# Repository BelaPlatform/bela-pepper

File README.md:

# PEPPER

Pepper is a DIY solution for integrating Bela with modular and Eurorack synths. [Click here](https://github.com/BelaPlatform/bela-pepper/wiki) for more information.

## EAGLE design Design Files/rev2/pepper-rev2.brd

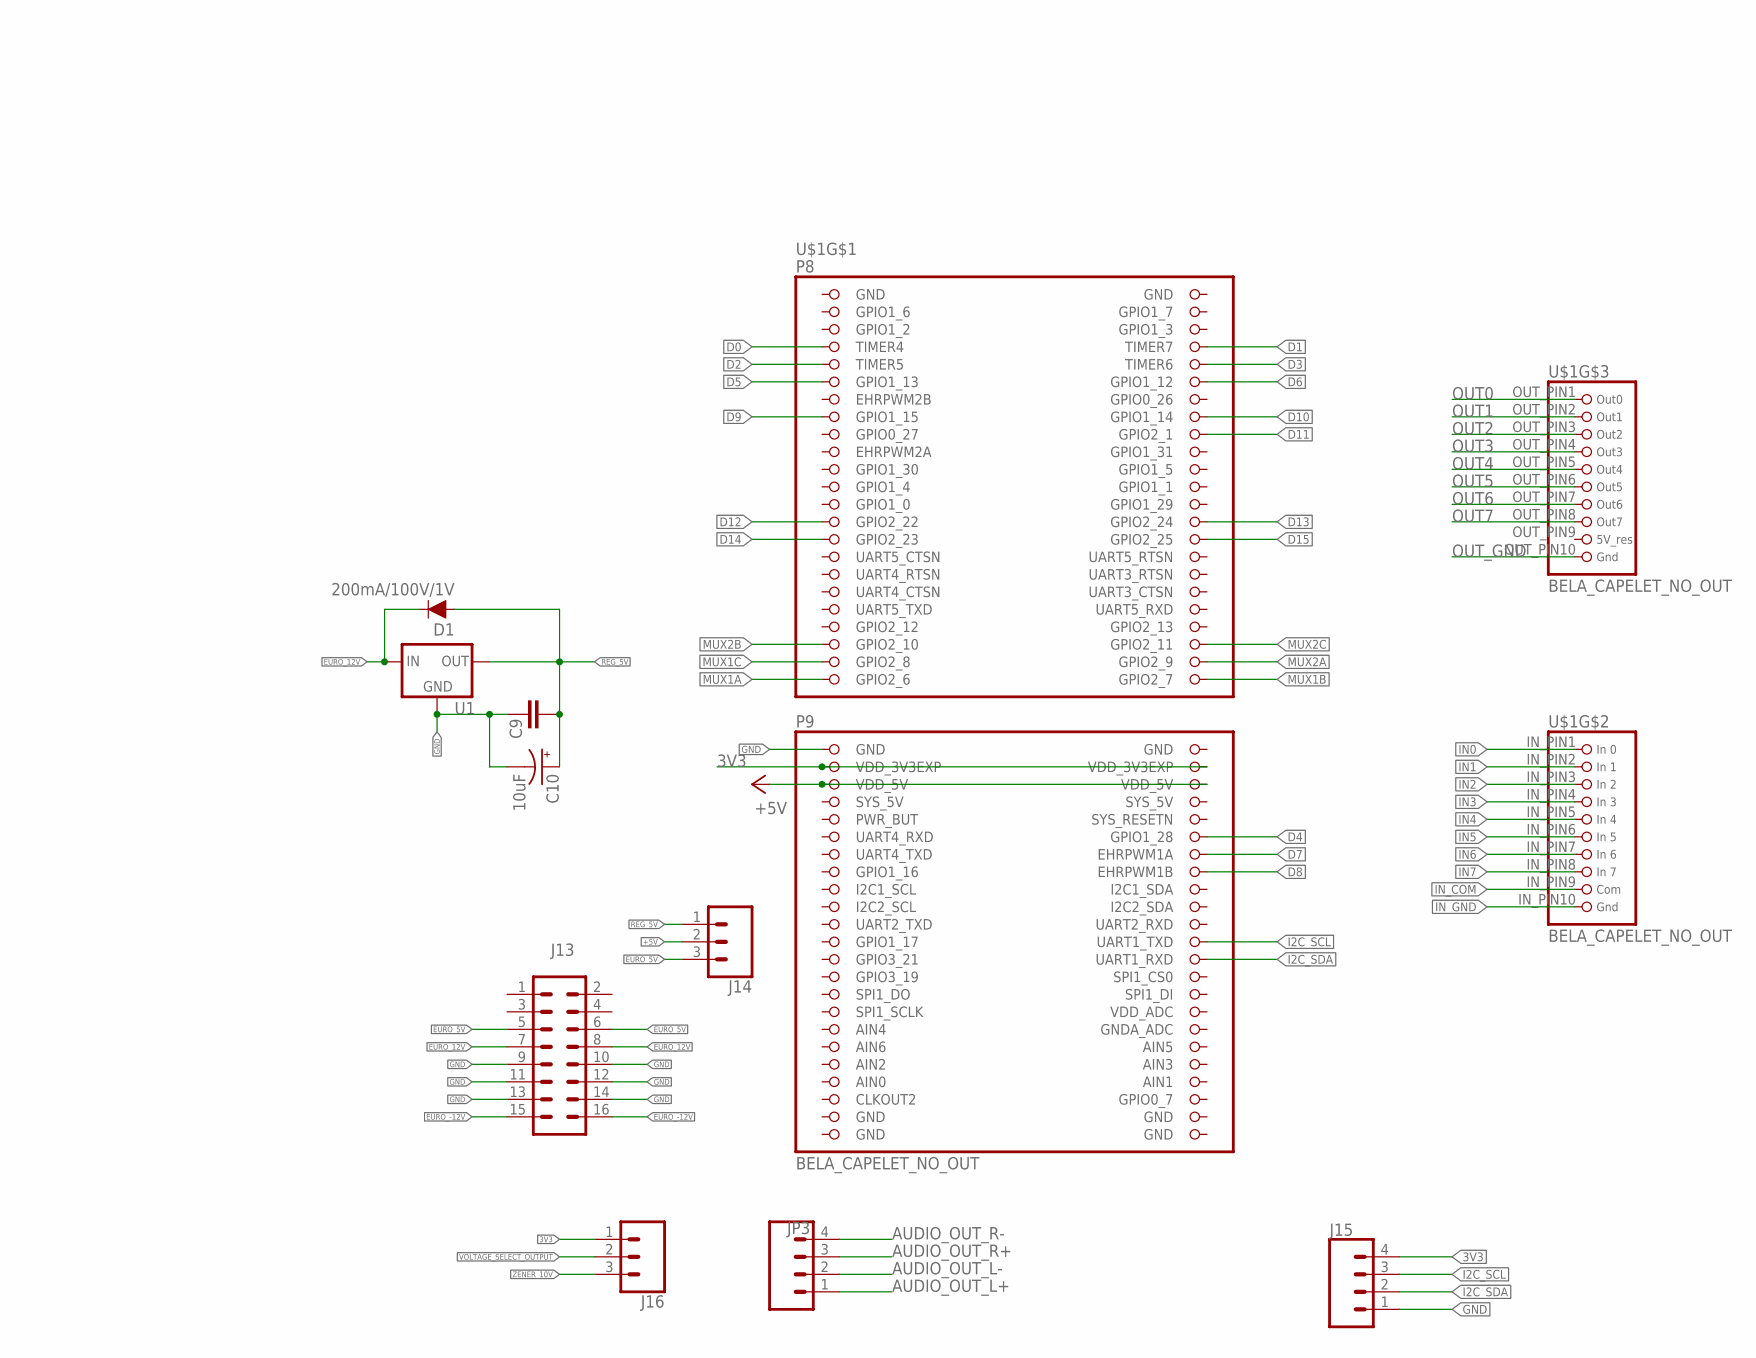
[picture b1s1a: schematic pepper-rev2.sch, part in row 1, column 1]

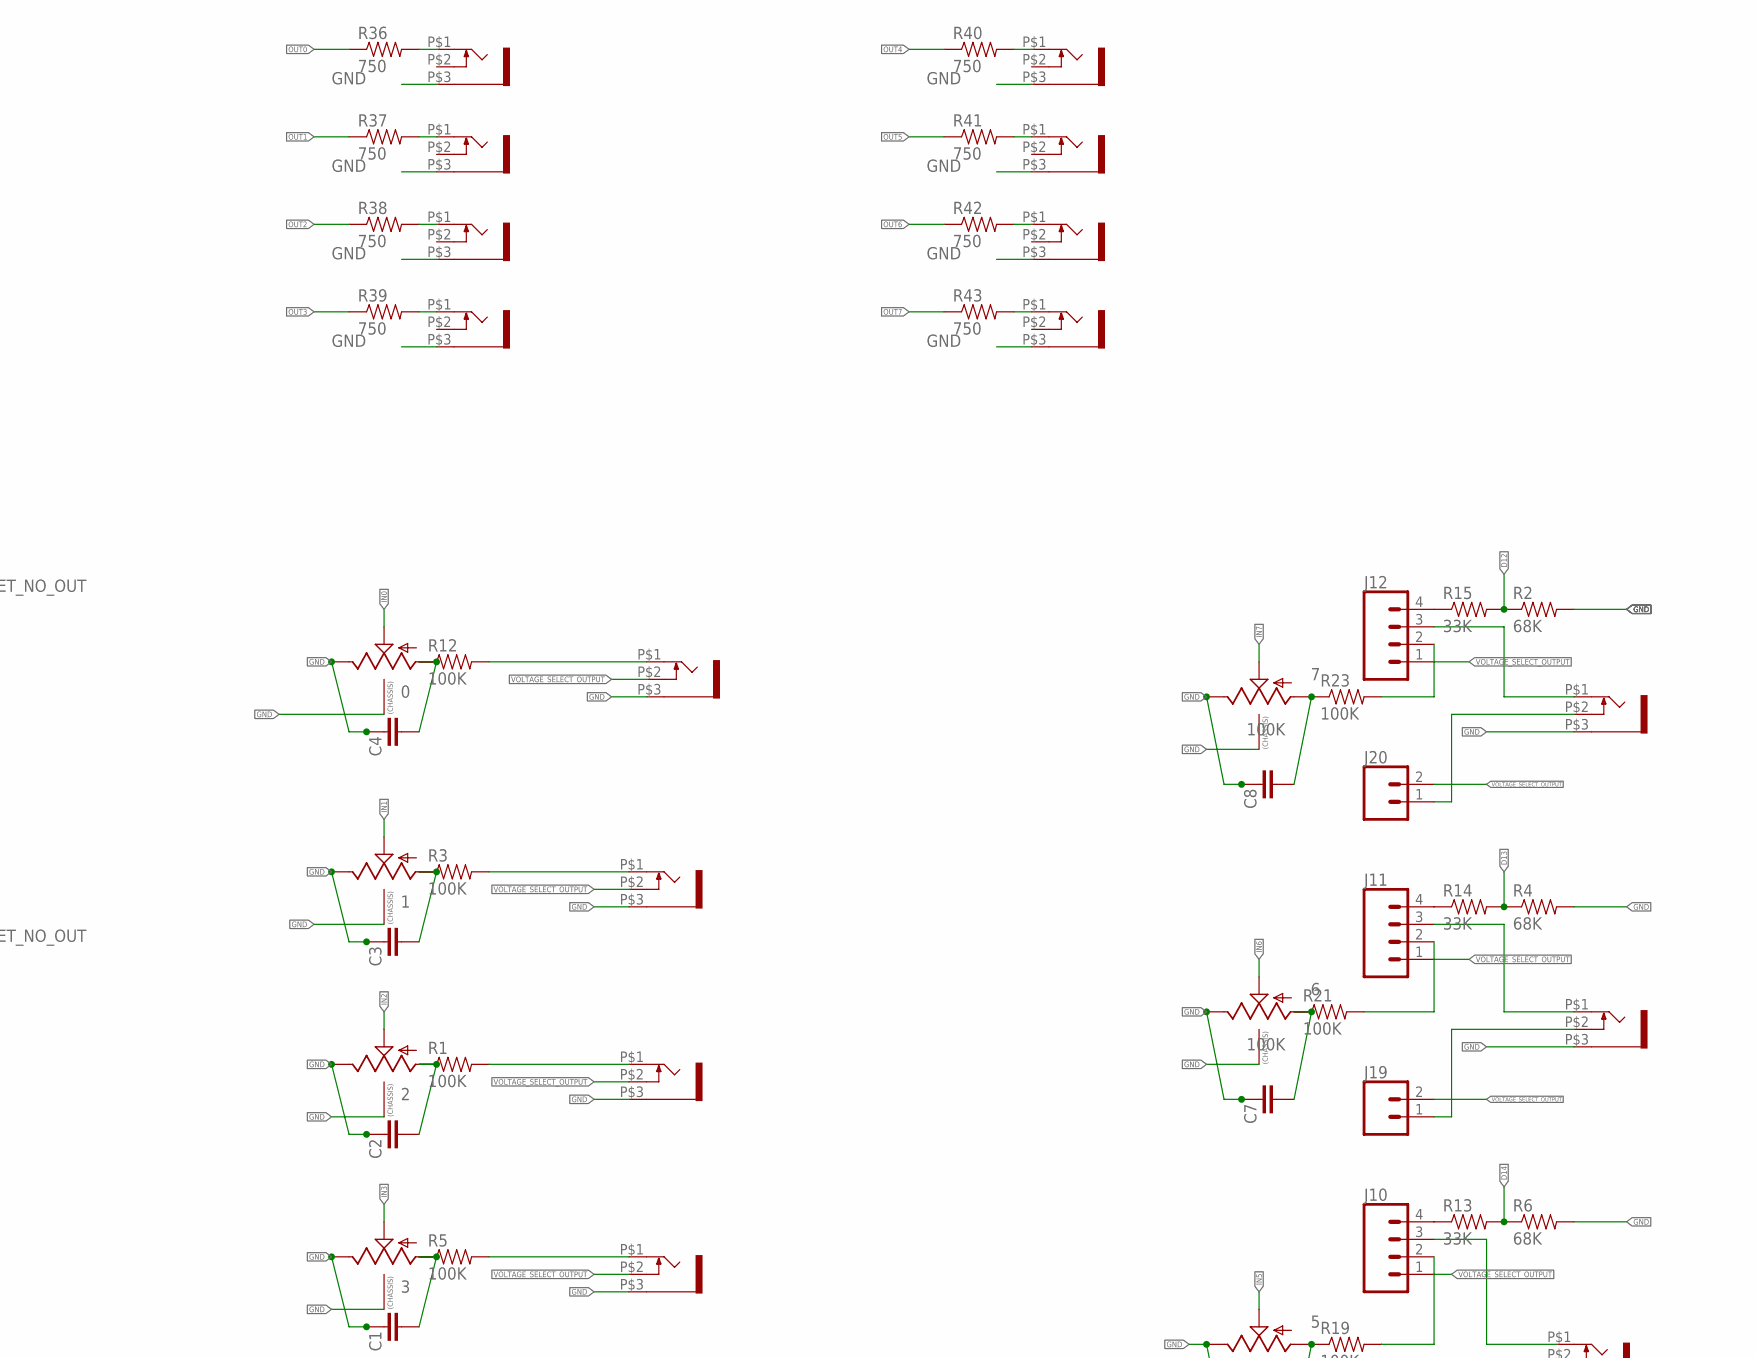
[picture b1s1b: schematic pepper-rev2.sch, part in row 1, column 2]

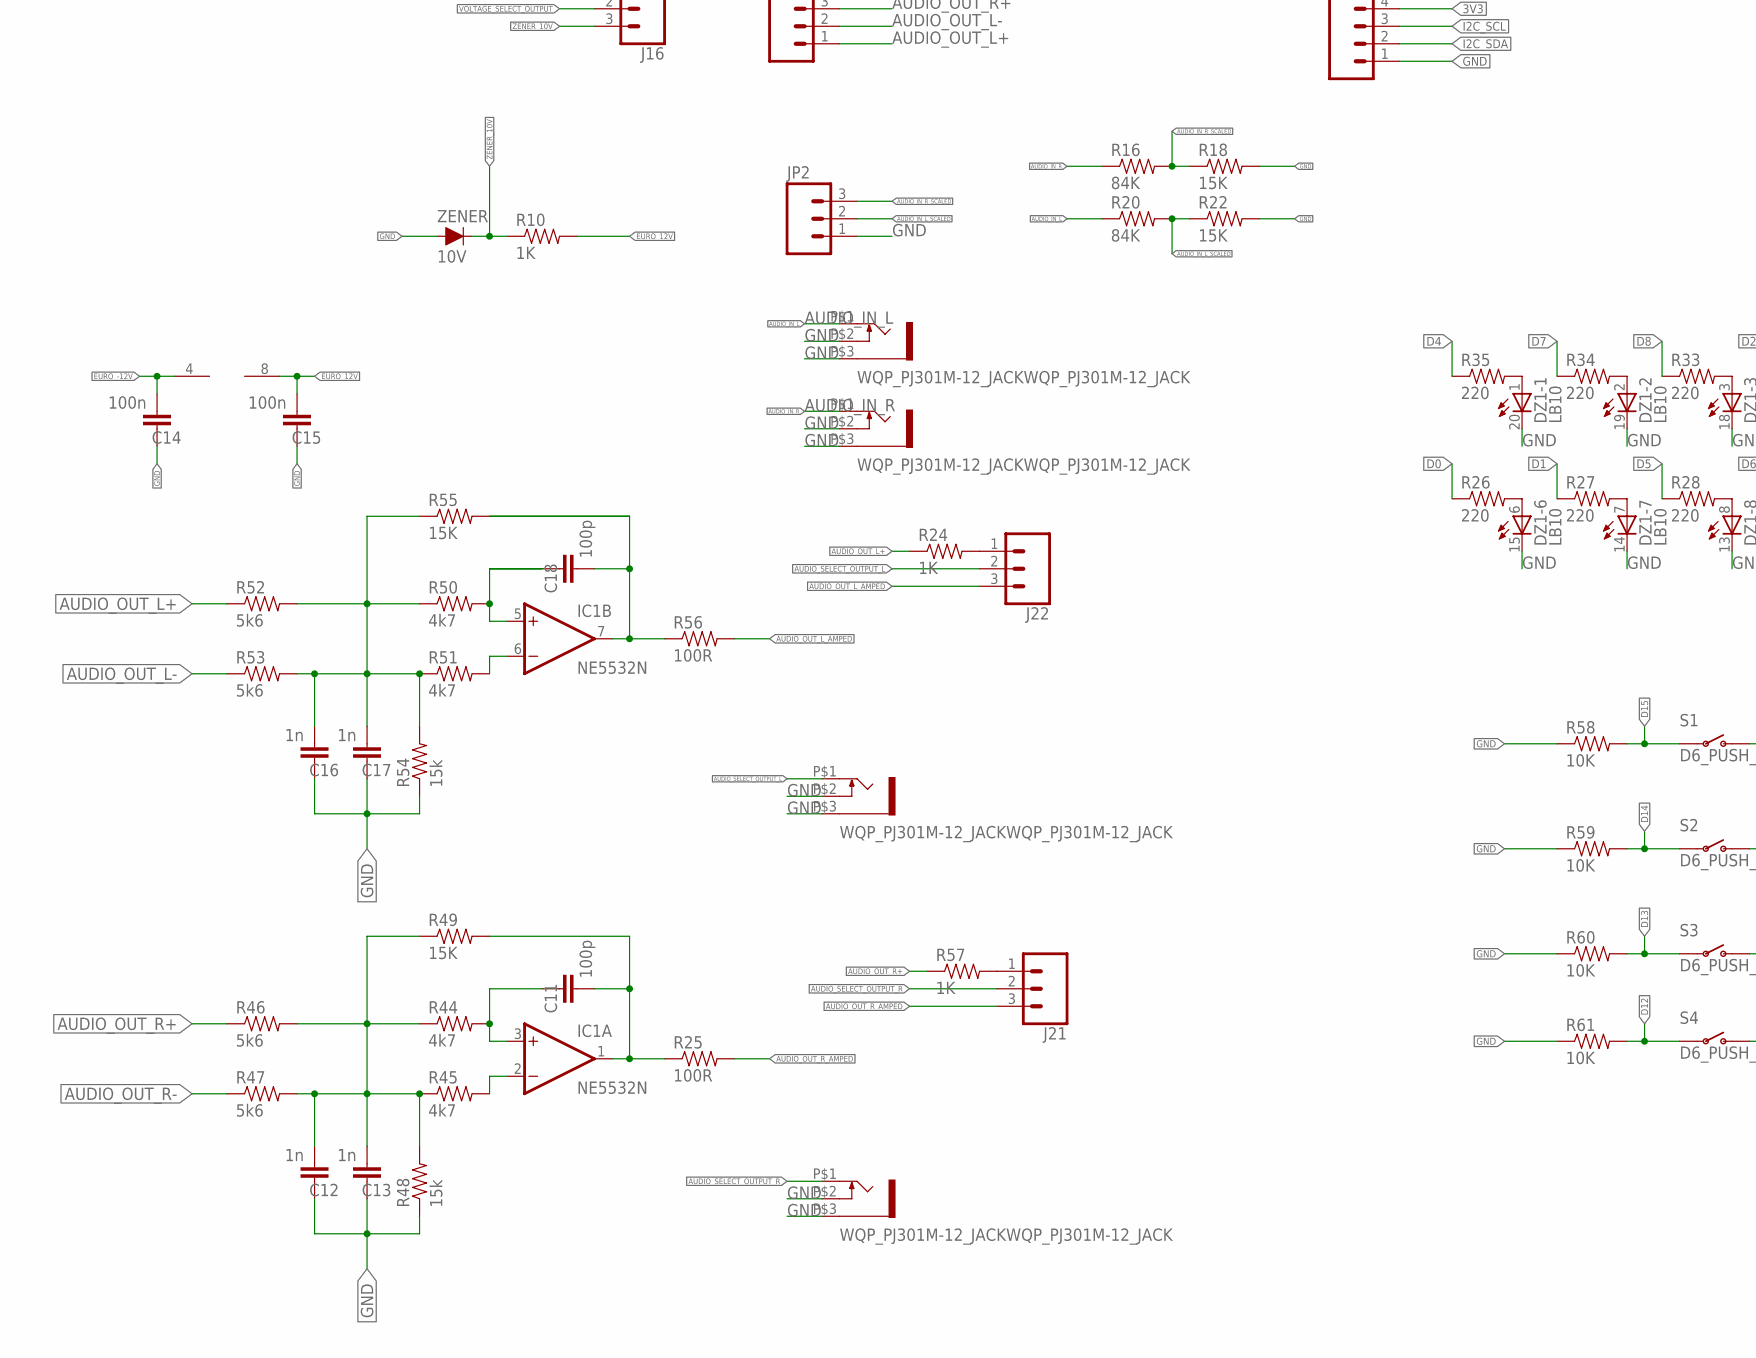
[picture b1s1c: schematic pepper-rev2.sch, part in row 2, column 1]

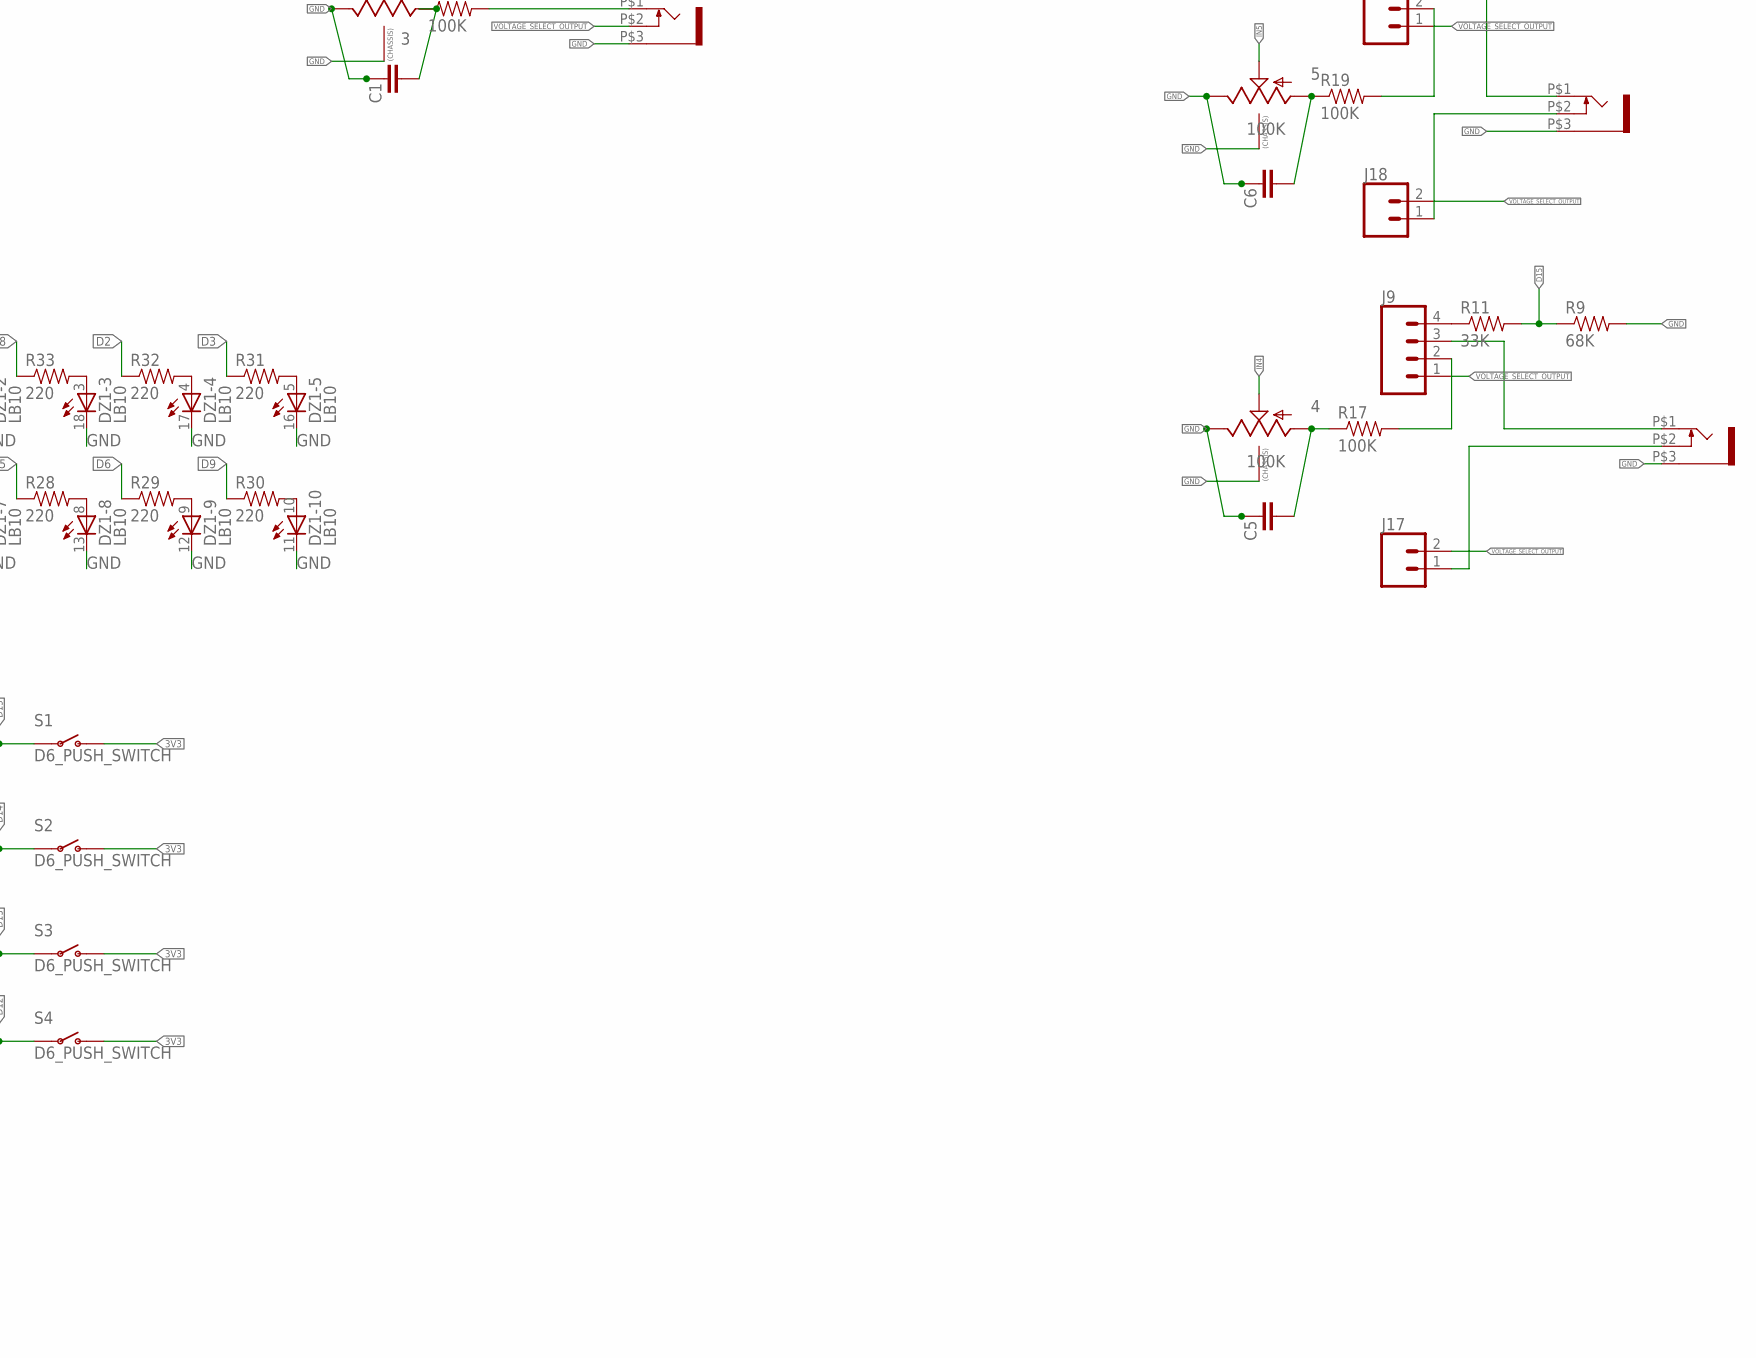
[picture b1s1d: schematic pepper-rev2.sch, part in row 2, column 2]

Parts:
0, 1, 2, 3: 9MM_SNAP-IN_POT_CHASSIS; 9MM_SNAP-IN_POT
4, 5, 6, 7: 100K; 9MM_SNAP-IN_POT
AUDIO_INPUT_L: WQP_PJ301M-12_JACKWQP_PJ301M-12_JACK; JACK-3.5
AUDIO_INPUT_R: WQP_PJ301M-12_JACKWQP_PJ301M-12_JACK; JACK-3.5
AUDIO_OUTPUT_L: WQP_PJ301M-12_JACKWQP_PJ301M-12_JACK; JACK-3.5
AUDIO_OUTPUT_R: WQP_PJ301M-12_JACKWQP_PJ301M-12_JACK; JACK-3.5
C1, C2, C3, C4, C5, C6, C7, C8, C9: CAPPTH; CAP-PTH-SMALL
C10: 10uF; CPOL-RADIAL-2.5MM-5MM
C11, C18: 100p; CAP-PTH-SMALL
C12, C13, C16, C17: 1n; CAP-PTH-SMALL
C14, C15: 100n; CAP-PTH-SMALL
D1: 200mA/100V/1V; DIODE-1N4148
DZ1: LB10
IC1: NE5532N; DIL08
J9, J10, J11, J12, J15: CONN_04PTH; 1X04
J13: 2X6 FEMALE; 2X8
J14, J16, J21, J22: CONN_03; 1X03
J17, J18, J19, J20: CONN_02; 1X02
JACK_IN_1, JACK_IN_2, JACK_IN_3, JACK_IN_4, JACK_IN_5, JACK_IN_6, JACK_IN_7, JACK_IN_8: WQP_PJ301M-12_JACKWQP_PJ301M-12_JACK; JACK-3.5
JACK_OUT_1, JACK_OUT_2, JACK_OUT_3, JACK_OUT_4, JACK_OUT_5, JACK_OUT_6, JACK_OUT_7, JACK_OUT_8: WQP_PJ301M-12_JACKWQP_PJ301M-12_JACK; JACK-3.5
JP2: M03PTH; 1X03@1
JP3: CONN_04; 1X04
R1, R3, R5, R12, R17, R19, R21, R23: 100K; AXIAL-0.3
R2, R4, R6, R9: 68K; AXIAL-0.3
R10, R24, R57: 1K; AXIAL-0.3
R11, R13, R14, R15: 33K; AXIAL-0.3
R16, R20: 84K; AXIAL-0.3
R18, R22, R49, R55: 15K; AXIAL-0.3
R25, R56: 100R; AXIAL-0.3
R26, R27, R28, R29, R30, R31, R32, R33, R34, R35: 220; AXIAL-0.3
R36, R37, R38, R39, R40, R41, R42, R43: 750; AXIAL-0.3
R44, R45, R50, R51: 4k7; AXIAL-0.3
R46, R47, R52, R53: 5k6; AXIAL-0.3
R48, R54: 15k; AXIAL-0.3
R58, R59, R60, R61: 10K; AXIAL-0.3
S1, S2, S3, S4: D6_PUSH_SWITCH
U1: V_REG_78XXSINK; TO220-IGO
U$1: BELA_CAPELET_NO_OUT; BELA_CAPELET_NO_OUTLINE
ZENER: 10V; DIODE-1N4001-KIT

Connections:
1: JACK_IN_3.P$1 (2), R1.P$2 (2)
2: JACK_IN_2.P$1 (2), R3.P$2 (2)
3: JACK_IN_1.P$1 (2), R12.P$2 (2)
3V3: J15.4, J16.1, S1.P$1 (O), S1.P$2 (O), S2.P$1 (O), S2.P$2 (O), S3.P$1 (O), S3.P$2 (O), S4.P$1 (O), S4.P$2 (O), U$1.49 (VDD_3V3EXP), U$1.50 (VDD_3V3EXP)
4: JACK_IN_4.P$1 (2), R5.P$2 (2)
+5V: J14.2, U$1.51 (VDD_5V), U$1.52 (VDD_5V)
AIN0: U$1.85 (AIN0)
AUDIO_IN_L: AUDIO_INPUT_L.P$1 (2), R20.P$1 (1)
AUDIO_IN_L_SCALED: JP2.2, R20.P$2 (2), R22.P$1 (1)
AUDIO_IN_R: AUDIO_INPUT_R.P$1 (2), R16.P$1 (1)
AUDIO_IN_R_SCALED: JP2.3, R16.P$2 (2), R18.P$1 (1)
AUDIO_OUT_L+: JP3.1, R24.P$1 (1), R52.P$1 (1)
AUDIO_OUT_L-: JP3.2, R53.P$1 (1)
AUDIO_OUT_L_AMPED: J22.3, R56.P$2 (2)
AUDIO_OUT_R+: JP3.3, R46.P$1 (1), R57.P$1 (1)
AUDIO_OUT_R-: JP3.4, R47.P$1 (1)
AUDIO_OUT_R_AMPED: J21.3, R25.P$2 (2)
AUDIO_SELECT_OUTPUT_L: AUDIO_OUTPUT_L.P$1 (2), J22.2
AUDIO_SELECT_OUTPUT_R: AUDIO_OUTPUT_R.P$1 (2), J21.2
D0: R26.P$1 (1), U$1.7 (TIMER4)
D1: R27.P$1 (1), U$1.8 (TIMER7)
D2: R32.P$1 (1), U$1.9 (TIMER5)
D3: R31.P$1 (1), U$1.10 (TIMER6)
D4: R35.P$1 (1), U$1.58 (GPIO1_28)
D5: R28.P$1 (1), U$1.11 (GPIO1_13)
D6: R29.P$1 (1), U$1.12 (GPIO1_12)
D7: R34.P$1 (1), U$1.60 (EHRPWM1A)
D8: R33.P$1 (1), U$1.62 (EHRPWM1B)
D9: R30.P$1 (1), U$1.15 (GPIO1_15)
D10: U$1.16 (GPIO1_14)
D11: U$1.18 (GPIO2_1)
D12: R2.P$1 (1), R15.P$2 (2), R61.P$2 (2), S4.P$3, S4.P$4, U$1.27 (GPIO2_22)
D13: R4.P$1 (1), R14.P$2 (2), R60.P$2 (2), S3.P$3, S3.P$4, U$1.28 (GPIO2_24)
D14: R6.P$1 (1), R13.P$2 (2), R59.P$2 (2), S2.P$3, S2.P$4, U$1.29 (GPIO2_23)
D15: R9.P$1 (1), R11.P$2 (2), R58.P$2 (2), S1.P$3, S1.P$4, U$1.30 (GPIO2_25)
EURO_5V: J13.5, J13.6, J14.3
EURO_12V: C15.2, D1.C, IC1.8 (V+), J13.7, J13.8, R10.P$2 (2), U1.IN
EURO_-12V: C14.2, IC1.4 (V-), J13.15, J13.16
GND: 0.3 (E), 0.CHASSIS1, 0.CHASSIS2, 1.3 (E), 1.CHASSIS1, 1.CHASSIS2, 2.3 (E), 2.CHASSIS1, 2.CHASSIS2, 3.3 (E), 3.CHASSIS1, 3.CHASSIS2, 4.3 (E), 4.CHASSIS1, 4.CHASSIS2, 5.3 (E), 5.CHASSIS1, 5.CHASSIS2, 6.3 (E), 6.CHASSIS1, 6.CHASSIS2, 7.3 (E), 7.CHASSIS1, 7.CHASSIS2, AUDIO_INPUT_L.P$2 (3), AUDIO_INPUT_L.P$3 (1), AUDIO_INPUT_R.P$2 (3), AUDIO_INPUT_R.P$3 (1), AUDIO_OUTPUT_L.P$2 (3), AUDIO_OUTPUT_L.P$3 (1), AUDIO_OUTPUT_R.P$2 (3), AUDIO_OUTPUT_R.P$3 (1), C1.1, C2.1, C3.1, C4.1, C5.1, C6.1, C7.1, C8.1, C9.1, C10.2 (-), C12.1, C13.1, C14.1, C15.1, C16.1, C17.1, DZ1.11 (C), DZ1.12 (C), DZ1.13 (C), DZ1.14 (C), DZ1.15 (C), DZ1.16 (C), DZ1.17 (C), DZ1.18 (C), DZ1.19 (C), DZ1.20 (C), J13.9, J13.10, J13.11, J13.12, J13.13, J13.14, J15.1, JACK_IN_1.P$3 (1), JACK_IN_2.P$3 (1), JACK_IN_3.P$3 (1), JACK_IN_4.P$3 (1), JACK_IN_5.P$3 (1), JACK_IN_6.P$3 (1), JACK_IN_7.P$3 (1), JACK_IN_8.P$3 (1), JACK_OUT_1.P$3 (1), JACK_OUT_2.P$3 (1), JACK_OUT_3.P$3 (1), JACK_OUT_4.P$3 (1), JACK_OUT_5.P$3 (1), JACK_OUT_6.P$3 (1), JACK_OUT_7.P$3 (1), JACK_OUT_8.P$3 (1), JP2.1, R2.P$2 (2), R4.P$2 (2), R6.P$2 (2), R9.P$2 (2), R18.P$2 (2), R22.P$2 (2), R48.P$1 (1), R54.P$1 (1), R58.P$1 (1), R59.P$1 (1), R60.P$1 (1), R61.P$1 (1), U1.GND, U$1.1 (GND), U$1.2 (GND), U$1.47 (GND), U$1.48 (GND), U$1.89 (GND), U$1.90 (GND), U$1.91 (GND), U$1.92 (GND), ZENER.A
I2C_SCL: J15.3, U$1.70 (UART1_TXD)
I2C_SDA: J15.2, U$1.72 (UART1_RXD)
IN0: 0.2 (S), U$1.IN_PIN1 (1)
IN1: 1.2 (S), U$1.IN_PIN2 (2)
IN2: 2.2 (S), U$1.IN_PIN3 (3)
IN3: 3.2 (S), U$1.IN_PIN4 (4)
IN4: 4.2 (S), U$1.IN_PIN5 (5)
IN5: 5.2 (S), U$1.IN_PIN6 (6)
IN6: 6.2 (S), U$1.IN_PIN7 (7)
IN7: 7.2 (S), U$1.IN_PIN8 (8)
IN_COM: U$1.IN_PIN9 (9)
IN_GND: U$1.IN_PIN10 (10)
MUX1A: U$1.45 (GPIO2_6)
MUX1B: U$1.46 (GPIO2_7)
MUX1C: U$1.43 (GPIO2_8)
MUX2A: U$1.44 (GPIO2_9)
MUX2B: U$1.41 (GPIO2_10)
MUX2C: U$1.42 (GPIO2_11)
unnamed: J10.3, JACK_IN_6.P$1 (2)
unnamed: DZ1.6 (A), R26.P$2 (2)
unnamed: DZ1.7 (A), R27.P$2 (2)
unnamed: DZ1.8 (A), R28.P$2 (2)
unnamed: DZ1.9 (A), R29.P$2 (2)
unnamed: DZ1.10 (A), R30.P$2 (2)
unnamed: DZ1.5 (A), R31.P$2 (2)
unnamed: DZ1.4 (A), R32.P$2 (2)
unnamed: DZ1.3 (A), R33.P$2 (2)
unnamed: DZ1.2 (A), R34.P$2 (2)
unnamed: DZ1.1 (A), R35.P$2 (2)
unnamed: 1.1 (A), C3.2, R3.P$1 (1)
unnamed: J12.2, R23.P$2 (2)
unnamed: J11.3, JACK_IN_7.P$1 (2)
unnamed: 6.1 (A), C7.2, R21.P$1 (1)
unnamed: J9.2, R17.P$2 (2)
unnamed: 5.1 (A), C6.2, R19.P$1 (1)
unnamed: J9.3, JACK_IN_5.P$1 (2)
unnamed: J12.3, JACK_IN_8.P$1 (2)
unnamed: 4.1 (A), C5.2, R17.P$1 (1)
unnamed: J10.4, R13.P$1 (1)
unnamed: J12.4, R15.P$1 (1)
unnamed: J9.4, R11.P$1 (1)
unnamed: J10.2, R19.P$2 (2)
unnamed: J11.2, R21.P$2 (2)
unnamed: J11.4, R14.P$1 (1)
unnamed: C18.1, IC1.5 (+IN), R50.P$2 (2)
unnamed: J22.1, R24.P$2 (2)
unnamed: J17.1, JACK_IN_5.P$2 (3)
unnamed: JACK_OUT_1.P$1 (2), R36.P$2 (2)
unnamed: J19.1, JACK_IN_7.P$2 (3)
unnamed: J18.1, JACK_IN_6.P$2 (3)
unnamed: J20.1, JACK_IN_8.P$2 (3)
unnamed: JACK_OUT_2.P$1 (2), R37.P$2 (2)
unnamed: JACK_OUT_3.P$1 (2), R38.P$2 (2)
unnamed: JACK_OUT_4.P$1 (2), R39.P$2 (2)
unnamed: JACK_OUT_5.P$1 (2), R40.P$2 (2)
unnamed: JACK_OUT_6.P$1 (2), R41.P$2 (2)
unnamed: JACK_OUT_7.P$1 (2), R42.P$2 (2)
unnamed: JACK_OUT_8.P$1 (2), R43.P$2 (2)
unnamed: C11.1, IC1.3 (+IN), R44.P$2 (2)
unnamed: IC1.2 (-IN), R45.P$2 (2)
unnamed: C11.2, IC1.1 (OUT), R25.P$1 (1), R49.P$2 (2)
unnamed: IC1.6 (-IN), R51.P$2 (2)
unnamed: C12.2, C13.2, R44.P$1 (1), R45.P$1 (1), R46.P$2 (2), R47.P$2 (2), R48.P$2 (2), R49.P$1 (1)
unnamed: C16.2, C17.2, R50.P$1 (1), R51.P$1 (1), R52.P$2 (2), R53.P$2 (2), R54.P$2 (2), R55.P$1 (1)
unnamed: C18.2, IC1.7 (OUT), R56.P$1 (1)
unnamed: J21.1, R57.P$2 (2)
OUT0: R36.P$1 (1), U$1.OUT_PIN1 (1)
OUT1: R37.P$1 (1), U$1.OUT_PIN2 (2)
OUT2: R38.P$1 (1), U$1.OUT_PIN3 (3)
OUT3: R39.P$1 (1), U$1.OUT_PIN4 (4)
OUT4: R40.P$1 (1), U$1.OUT_PIN5 (5)
OUT5: R41.P$1 (1), U$1.OUT_PIN6 (6)
OUT6: R42.P$1 (1), U$1.OUT_PIN7 (7)
OUT7: R43.P$1 (1), U$1.OUT_PIN8 (8)
OUT_GND: U$1.OUT_PIN10 (10)
POT_IN1: 0.1 (A), C4.2, R12.P$1 (1)
POT_IN3: 2.1 (A), C2.2, R1.P$1 (1)
POT_IN4: 3.1 (A), C1.2, R5.P$1 (1)
POT_IN8: 7.1 (A), C8.2, R23.P$1 (1)
REG_5V: C9.2, C10.1 (+), D1.A, J14.1, U1.OUT
SYS_5V: U$1.53 (SYS_5V)
VOLTAGE_SELECT_OUTPUT: J9.1, J10.1, J11.1, J12.1, J16.2, J17.2, J18.2, J19.2, J20.2, JACK_IN_1.P$2 (3), JACK_IN_2.P$2 (3), JACK_IN_3.P$2 (3), JACK_IN_4.P$2 (3)
ZENER_10V: J16.3, R10.P$1 (1), ZENER.C

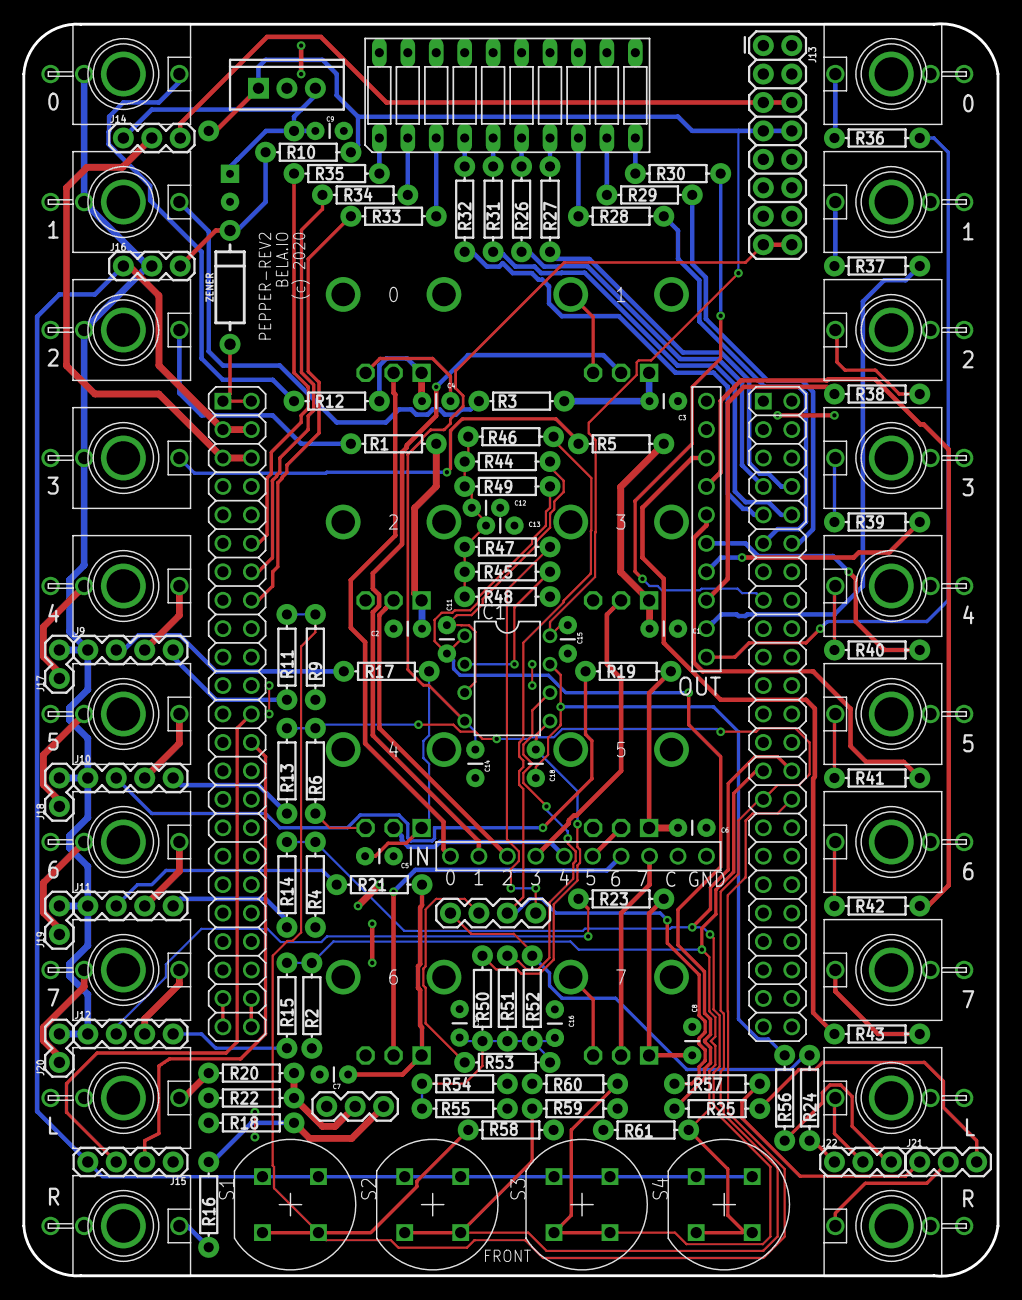
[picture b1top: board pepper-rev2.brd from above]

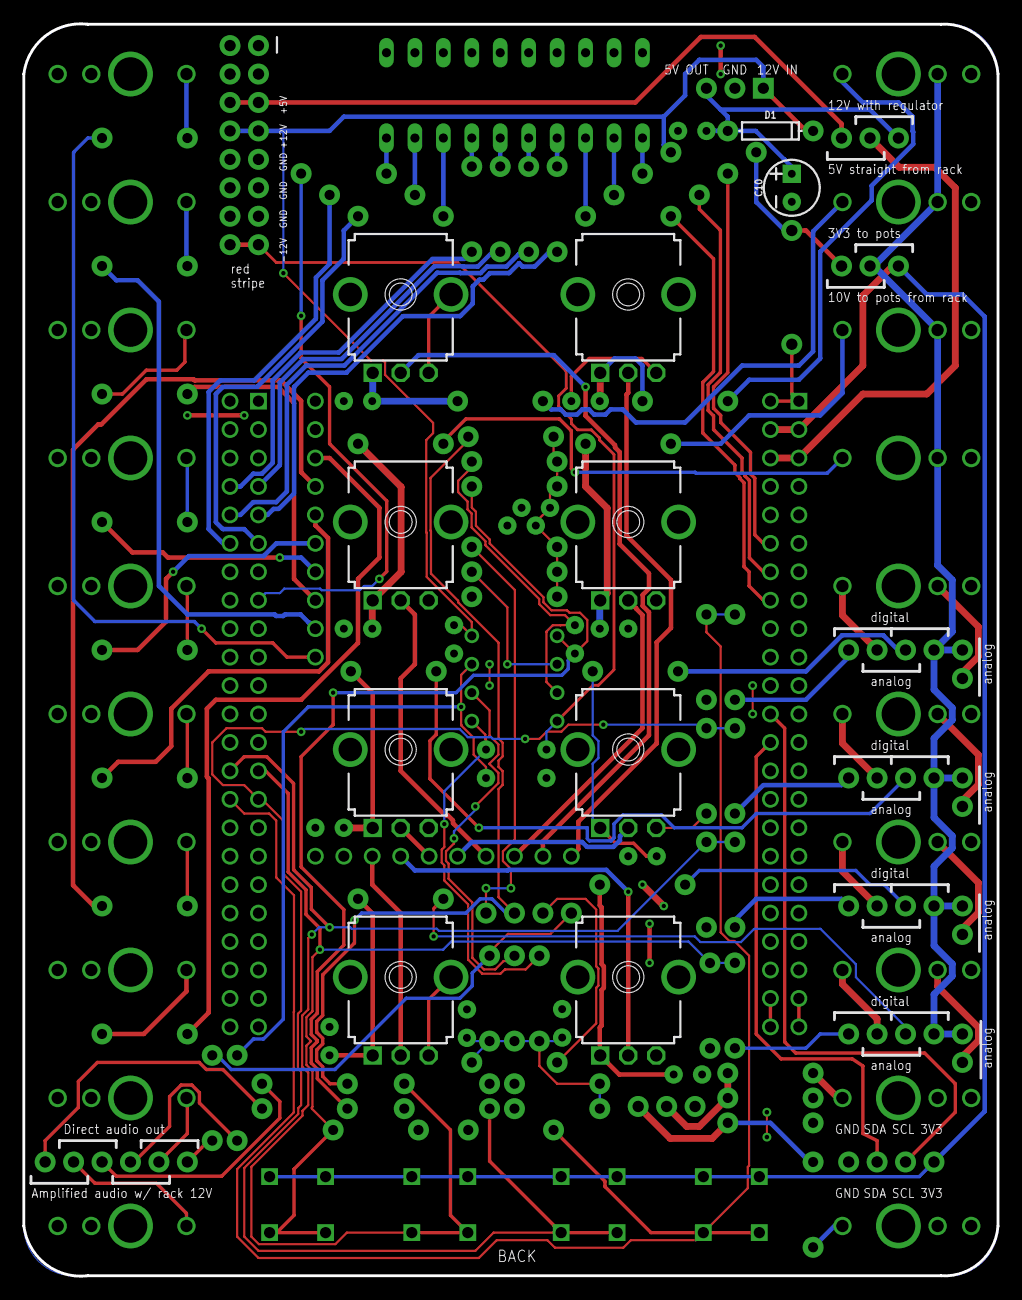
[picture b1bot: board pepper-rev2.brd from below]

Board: 2 copper layers, 87.0 x 111.8 mm, 131 parts (10 on the bottom side), 109 nets.

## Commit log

2019-07-02 Examples
2019-07-02 Added schematic, board and faceplate and cleaned examples.
2019-07-02 Example changes.
2020-07-13 rev2b files
2020-07-31 Pepper rev2 examples.
2020-07-31 removed old examples
2020-07-31 And another
2020-08-11 Missing abstractions.
2020-08-11 Examples updated.
2022-01-26 Added rev2 faceplate pdf
2022-09-14 Added design files
2022-12-15 Added schematic 2b

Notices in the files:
Design Files/rev2/pepper-rev2.brd:
(c) 2020
parts and their libraries:
SparkFun-Capacitors: Licensing: Creative Commons ShareAlike 4.0 International - https://creativecommons.org/licenses/by-sa/4.0
